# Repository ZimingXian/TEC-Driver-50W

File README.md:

# TEC-Driver-50W
https://oshwhub.com/wesd/sc8903-5a-ke-diao-sheng-xiang-ya-mu-kuai

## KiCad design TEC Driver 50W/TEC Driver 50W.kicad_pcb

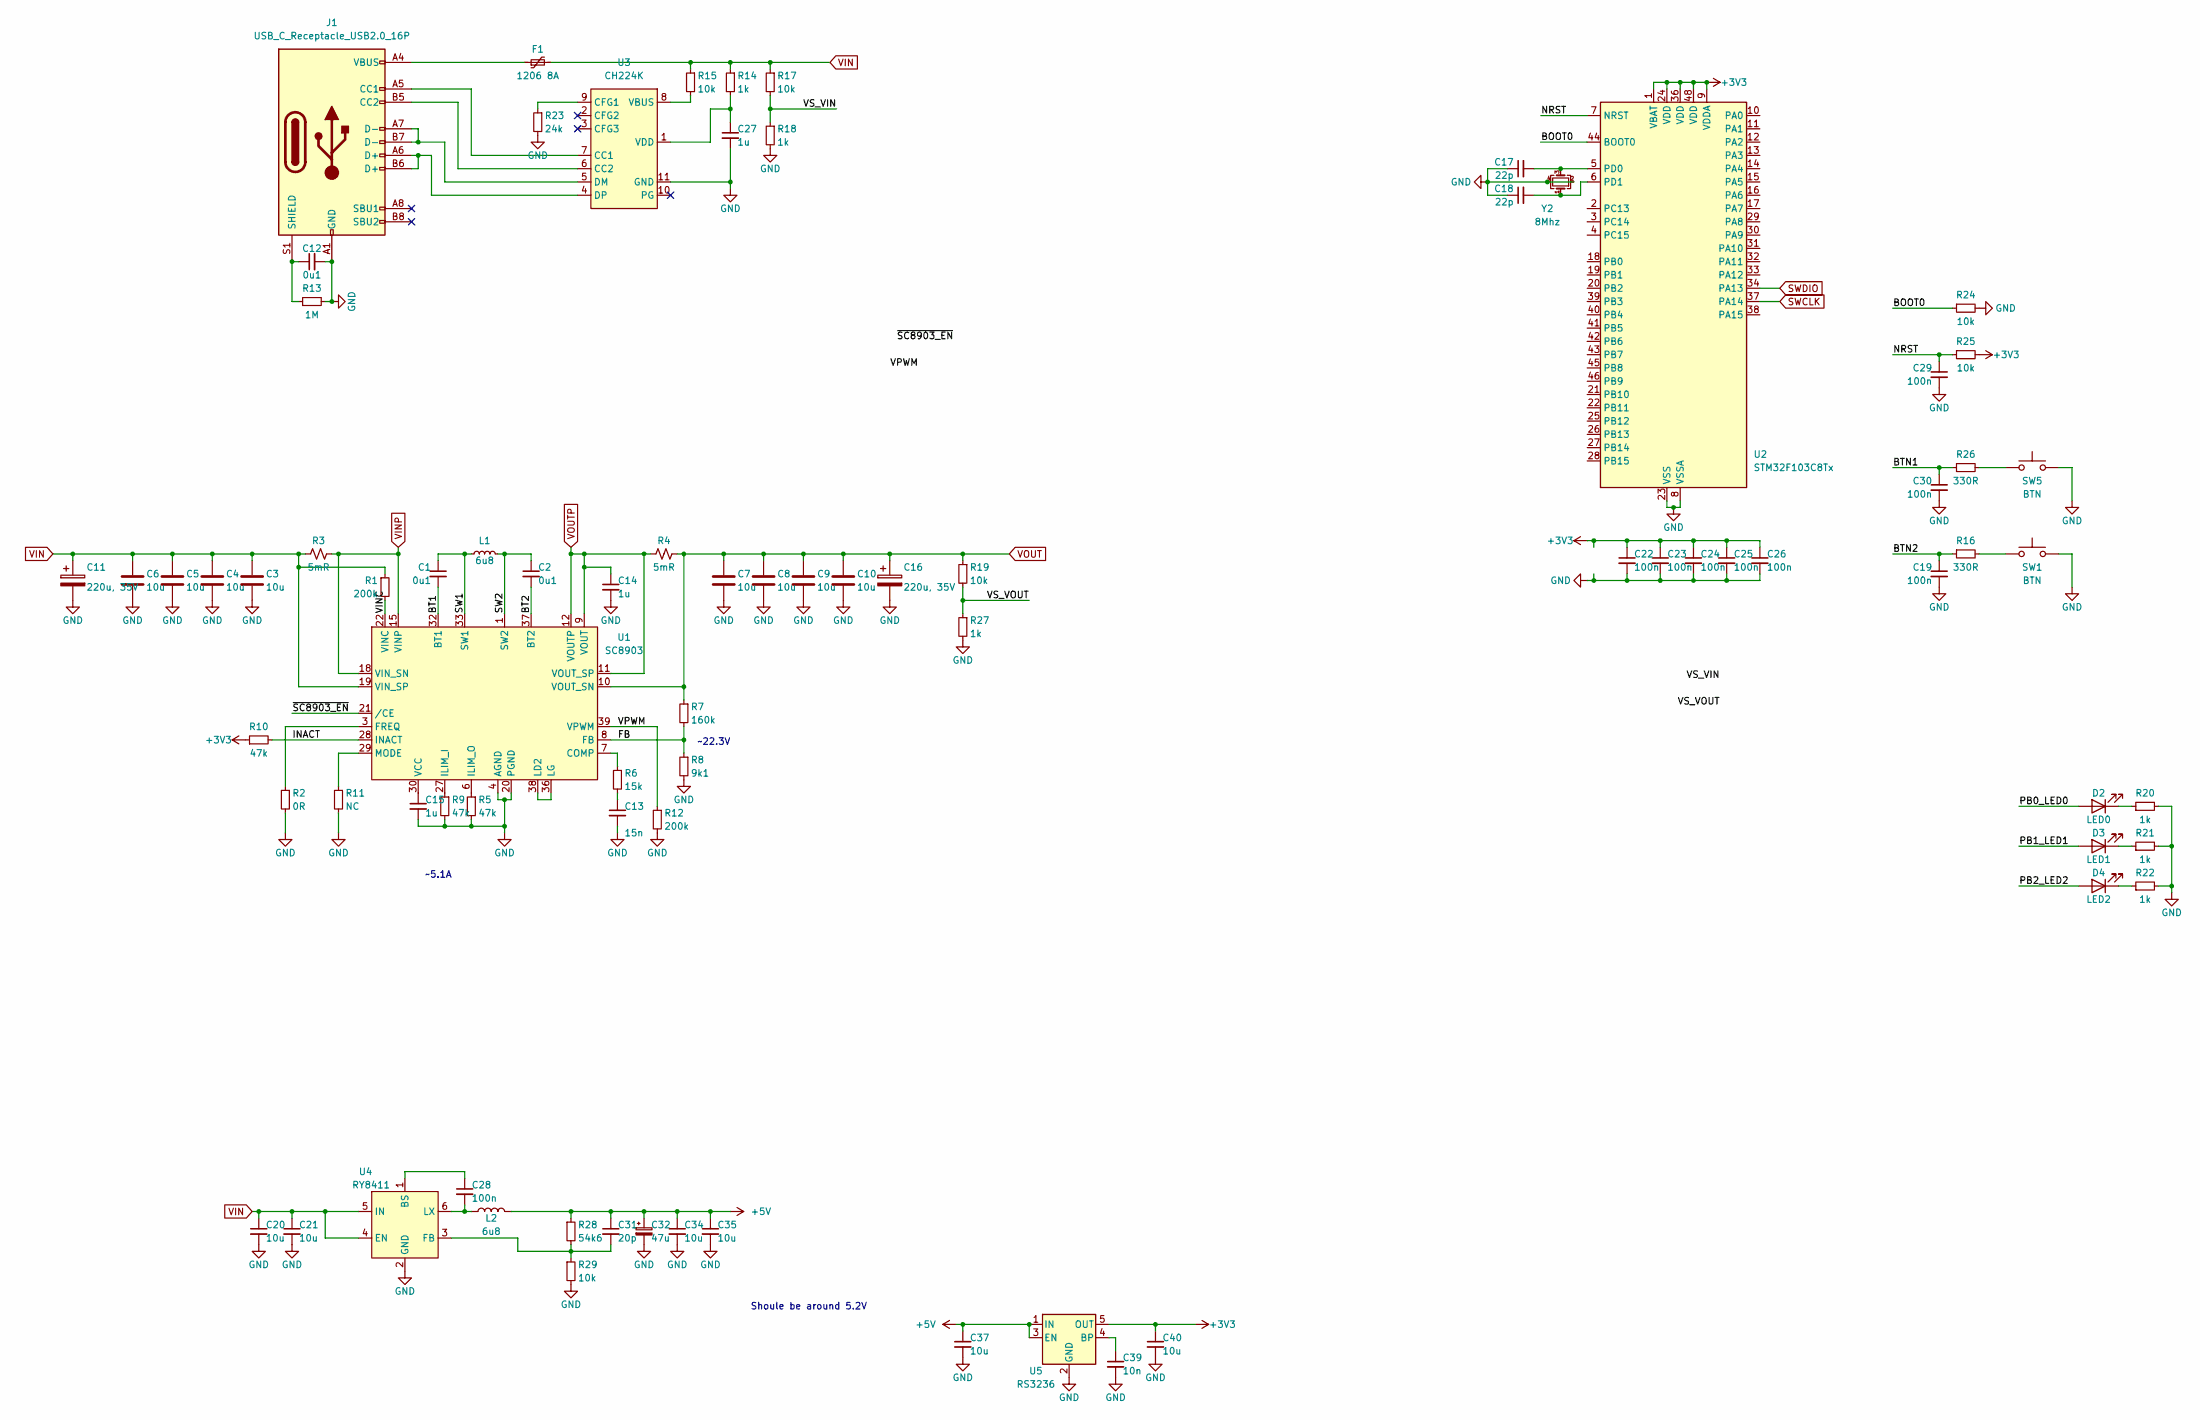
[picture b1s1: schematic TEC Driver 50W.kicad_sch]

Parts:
C1, C2, C12: 0u1; C_0603_1608Metric
C3, C4, C5, C6, C7, C8, C9, C10, C20, C21: 10u; C_1206_3216Metric
C11: 220u, 35V; Cap_Al_D6.3xH11.5mm_Hor_Flip
C13: 15n; C_0603_1608Metric
C14, C15, C27: 1u; C_0603_1608Metric
C16: 220u, 35V; Cap_Al_D6.3xH11.5mm_Hor
C17, C18: 22p; C_0603_1608Metric
C19, C22, C23, C24, C25, C26, C28, C29, C30: 100n; C_0603_1608Metric
C31: 20p; C_0603_1608Metric
C32: 47u; CP_EIA-3216-18_Kemet-A_Pad1.58x1.35mm_HandSolder
C34, C35, C37, C40: 10u; C_0603_1608Metric
C39: 10n; C_0603_1608Metric
D2: LED0; LED_0603_1608Metric
D3: LED1; LED_0603_1608Metric
D4: LED2; LED_0603_1608Metric
F1: 1206 8A; Fuse_1206_3216Metric
J1: USB_C_Receptacle_USB2.0_16P; USB_C_Receptacle_Palconn_UTC16-G
L1: 6u8; L_Sunlord_MWSA1004S
L2: 6u8; L_Sunlord_MWSA0402S
R1, R12: 200k; R_0603_1608Metric
R2: 0R; R_0603_1608Metric
R3, R4: 5mR; R_1206_3216Metric
R5, R9, R10: 47k; R_0603_1608Metric
R6: 15k; R_0603_1608Metric
R7: 160k; R_0603_1608Metric
R8: 9k1; R_0603_1608Metric
R11: NC; R_0603_1608Metric
R13: 1M; R_0603_1608Metric
R14, R18, R20, R21, R22, R27: 1k; R_0603_1608Metric
R15, R17, R19, R24, R25, R29: 10k; R_0603_1608Metric
R16, R26: 330R; R_0603_1608Metric
R23: 24k; R_0603_1608Metric
R28: 54k6; R_0603_1608Metric
SW1, SW5: BTN; SW_SPST_PTS810
U1: SC8903; QFN-40L(SC8903)
U2: STM32F103C8Tx; LQFP-48_7x7mm_P0.5mm
U3: CH224K; ESSOP-10_3.9x4.9mm_P1.00mm
U4: RY8411; SOT-23-6
U5: RS3236; SOT-23-5
Y2: 8Mhz; Crystal_SMD_3225-4Pin_3.2x2.5mm

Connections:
+3V3: C22.1, C23.1, C24.1, C25.1, C26.1, C40.1, R10.1, R25.2, U2.1 (VBAT), U2.9 (VDDA), U2.24 (VDD), U2.36 (VDD), U2.48 (VDD), U5.5 (OUT)
+5V: C31.1, C32.1, C34.1, C35.1, C37.1, L2.2, R28.1, U5.1 (IN), U5.3 (EN)
/BOOT0: R24.1, U2.44 (BOOT0)
/BT1: C1.2, U1.32 (BT1)
/BT2: C2.2, U1.37 (BT2)
/BTN1: C30.1, R26.1
/BTN2: C19.1, R16.1
/FB: R7.2, R8.1, U1.8 (FB)
/INACT: R10.2, U1.28 (INACT)
/NRST: C29.1, R25.1, U2.7 (NRST)
/PB0_LED0: D2.2 (A)
/PB1_LED1: D3.2 (A)
/PB2_LED2: D4.2 (A)
/SW1: C1.1, L1.1, U1.33 (SW1), U1.34 (SW1), U1.35 (SW1)
/SW2: C2.1, L1.2, U1.1 (SW2), U1.2 (SW2), U1.40 (SW2)
/VINC: R1.2, U1.22 (VINC)
/VPWM: R12.1, U1.39 (VPWM)
/VS_VIN: R17.2, R18.1
/VS_VOUT: R19.2, R27.1
/~SC8903_EN: U1.21 (/CE)
GND: C3.2, C4.2, C5.2, C6.2, C7.2, C8.2, C9.2, C10.2, C11.2, C12.2, C13.2, C14.2, C15.2, C16.2, C17.1, C18.1, C19.2, C20.2, C21.2, C22.2, C23.2, C24.2, C25.2, C26.2, C27.2, C29.2, C30.2, C32.2, C34.2, C35.2, C37.2, C39.2, C40.2, J1.A1 (GND), J1.A12 (GND), J1.B1 (GND), J1.B12 (GND), R2.2, R5.2, R8.2, R9.2, R11.2, R12.2, R13.2, R18.2, R20.2, R21.2, R22.2, R23.2, R24.2, R27.2, R29.2, SW1.2, SW5.2, U1.4 (AGND), U1.20 (PGND), U1.23 (PGND), U1.24 (PGND), U1.25 (PGND), U1.26 (PGND), U2.8 (VSSA), U2.23 (VSS), U2.35 (VSS), U2.47 (VSS), U3.11 (GND), U4.2 (GND), U5.2 (GND), Y2.2, Y2.4
unnamed: C13.1, R6.2
unnamed: D2.1 (K), R20.1
unnamed: D3.1 (K), R21.1
unnamed: D4.1 (K), R22.1
unnamed: F1.1, J1.A4 (VBUS), J1.A9 (VBUS), J1.B4 (VBUS), J1.B9 (VBUS)
unnamed: J1.A5 (CC1), U3.7 (CC1)
unnamed: J1.B5 (CC2), U3.6 (CC2)
unnamed: C12.1, J1.S1 (SHIELD), R13.1
unnamed: R16.2, SW1.1
unnamed: R26.2, SW5.1
unnamed: R6.1, U1.7 (COMP)
unnamed: R2.1, U1.3 (FREQ)
unnamed: R9.1, U1.27 (ILIM_I)
unnamed: R5.1, U1.6 (ILIM_O)
unnamed: U1.36 (LG), U1.38 (LD2)
unnamed: R11.1, U1.29 (MODE)
unnamed: U1.5 (NC), U1.31 (NC)
unnamed: C15.1, U1.30 (VCC)
unnamed: C17.2, U2.5 (PD0), Y2.3
unnamed: C18.2, U2.6 (PD1), Y2.1
unnamed: R23.1, U3.9 (CFG1)
unnamed: J1.A7 (D-), J1.B7 (D-), U3.5 (DM)
unnamed: J1.A6 (D+), J1.B6 (D+), U3.4 (DP)
unnamed: R15.2, U3.8 (VBUS)
unnamed: C27.1, R14.2, U3.1 (VDD)
unnamed: C28.1, U4.1 (BS)
unnamed: C31.2, R28.2, R29.1, U4.3 (FB)
unnamed: C28.2, L2.1, U4.6 (LX)
unnamed: C39.1, U5.4 (BP)
SWCLK: U2.37 (PA14)
SWDIO: U2.34 (PA13)
VIN: C3.1, C4.1, C5.1, C6.1, C11.1, C20.1, C21.1, F1.2, R1.1, R3.1, R14.1, R15.1, R17.1, U1.19 (VIN_SP), U4.4 (EN), U4.5 (IN)
VINP: R3.2, U1.15 (VINP), U1.16 (VINP), U1.17 (VINP), U1.18 (VIN_SN)
VOUT: C7.1, C8.1, C9.1, C10.1, C16.1, R4.2, R7.1, R19.1, U1.10 (VOUT_SN)
VOUTP: C14.1, R4.1, U1.9 (VOUT), U1.11 (VOUT_SP), U1.12 (VOUTP), U1.13 (VOUTP), U1.14 (VOUTP)

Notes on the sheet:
Shoule be around 5.2V
~22.3V
~5.1A

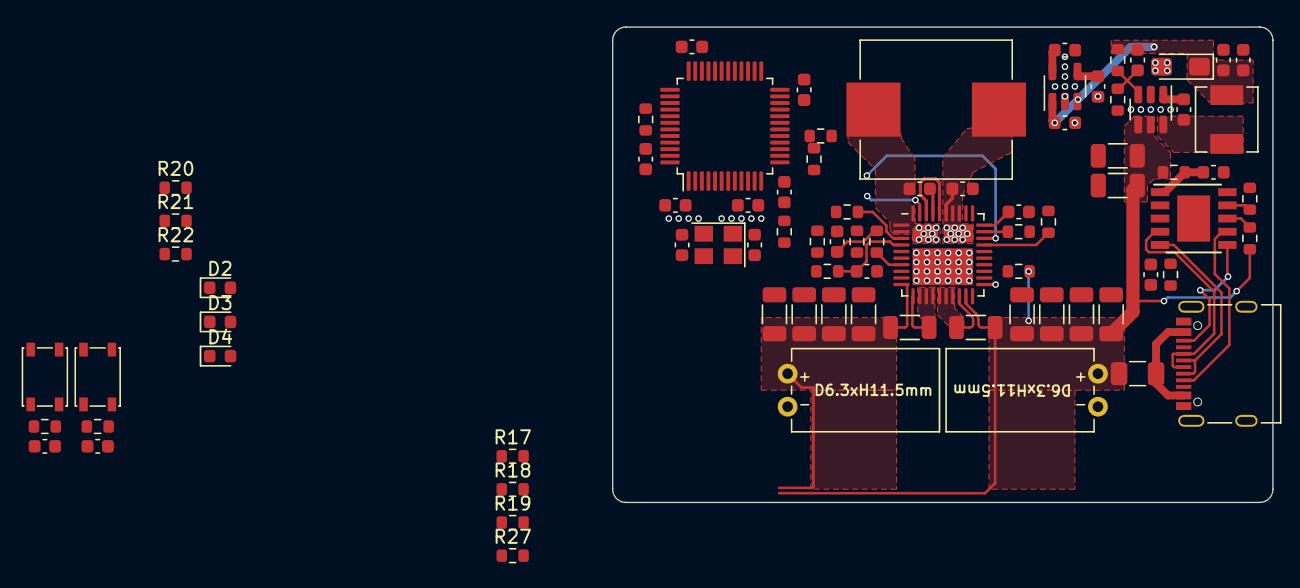
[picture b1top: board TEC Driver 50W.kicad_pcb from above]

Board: 2 copper layers, 50.0 x 36.0 mm, 81 parts (0 on the bottom side), 50 nets.

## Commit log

2024-04-18 04/18
2024-04-18 4/18
